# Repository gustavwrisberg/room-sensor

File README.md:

# Room Sensor Lite

A small, low-cost Home Assistant room sensor: **mmWave presence, temperature, humidity and light** on one fully assembled board, in a 3D-printed case that mounts on a wall, a ceiling, a room corner or a desk foot.

Runs [ESPHome](https://esphome.io), plugs in over USB-C, and is designed so the whole board can be assembled by JLCPCB with **Economic PCBA**: no soldering needed, you only screw the case shut.

## Features

| | |
|---|---|
| Presence | Hi-Link **HLK-LD2410C** 24 GHz radar, moving + still targets, ~6 m, ±60° |
| Temperature / humidity | **SHT40**-compatible sensor (Nyfea SHT40-N-NF) in its own vented chamber |
| Window detection | Template sensor in ESPHome: flags a sudden temperature drop |
| Light | **BH1750** behind a light tube and front window |
| MCU | **Seeed XIAO ESP32C6**: Wi-Fi 6, BLE, Thread-capable, onboard antenna + U.FL option |
| Power | 5 V over the XIAO's USB-C |
| Board | 43.3 × 22 mm, 2 layers, single-sided assembly |
| Case | 76 × 29 × 16 mm, resin print, 2 × M3×12 screws, keyholes in the back |

> IKEA MYGGBETT door/window sensors are deliberately **not** used: windows/doors are detected from the temperature drop instead.

## Repository layout

```
hardware/kicad/        KiCad 10 project (schematic + PCB)
hardware/production/   Gerbers, BOM and pick-and-place for JLCPCB
enclosure/             Parametric case (Python + manifold3d) and ready-made STLs
firmware/              ESPHome configuration
docs/                  Images
```

## Bill of materials

All parts are fitted by JLCPCB (Economic PCBA, top side).

| Ref | Part | LCSC | Note |
|---|---|---|---|
| U2 | Seeed XIAO ESP32C6 | C27675191 | castellated, soldered flat |
| SM1 | HLK-LD2410C-P radar | C19723500 | pin header, overhangs the left board edge |
| U1 | Nyfea SHT40-N-NF | C54946589 | I2C 0x44 |
| U4 | ROHM BH1750FVI-TR | C78960 | I2C 0x23, exposed pad not soldered |
| C7 | 10 µF 0805 | C15850 | radar 5 V |
| C9, C11, C12 | 100 nF 0402 | C1525 | C12 = BH1750 DVI power-up reset |
| R8, R9 | 4.7 kΩ 0402 | C25900 | I2C pull-ups |

> The exported `hardware/production/bom.csv` has an empty LCSC field for U2. Enter **C27675191** for it when uploading to JLCPCB (or add the LCSC field to the XIAO symbol before re-exporting).

Per case: 2 × M3×12 socket-head screws (DIN 912, e.g. JLCMC EDLA-J2-M3-L12).

**Approximate cost** (5 units, Oct 2026, incl. shipping, excl. VAT): ≈ $22 per assembled board, plus the case print.

## Pin map (XIAO ESP32C6)

| XIAO | GPIO | Net |
|---|---|---|
| D2 | GPIO2 | RADAR_OUT |
| D3 | GPIO21 | BH1750 DVI |
| D4 | GPIO22 | SDA |
| D5 | GPIO23 | SCL |
| D6 | GPIO16 | ESP TX → radar RX |
| D7 | GPIO17 | ESP RX ← radar TX |
| 5V | VBUS | radar VCC |
| 3V3 | 3.3 V | SHT40, BH1750, pull-ups |

GPIO3 / GPIO14 are used internally by the XIAO's RF switch (set in the ESPHome config).

## Ordering the board (JLCPCB)

1. Upload `hardware/production/gerbers.zip`: 2 layers, 1.6 mm, **LeadFree HASL**.
2. Enable PCB assembly → **Economic**, top side.
3. Upload `bom.csv` and `positions.csv`. Set U2 to C27675191.
4. In the placement preview, check:
   - the XIAO's USB-C points out over the bottom board edge
   - the radar's antenna side (gold patches) faces **up**
   - the pin-1 marks of U1 and U4

## Enclosure

The STLs in `enclosure/` are ready to print. Resin (e.g. JLC3DP 9600) is the default; SLS nylon also works (set `MATERIAL = "nylon"` for a tighter screw pilot hole).

| File | What |
|---|---|
| `lite_base.stl` | wall side: board pins, end bosses, USB-C opening, vents, keyholes |
| `lite_lid.stl` | room side: radar corner pads, light tube, SHT40 chamber + vents, screw posts |
| `lite_foot.stl` | desk stand, hooks into the keyholes |
| `lite_corner_mount.stl` | 45° wedge for a room corner (best radar coverage) |

Assembly: drop the board onto the three pins in the base, put the lid on, and fit the two M3×12 screws from the back.

To change anything, edit the parameters at the top of `room_sensor_case_lite.py` and run:

```bash
pip install manifold3d trimesh numpy
python room_sensor_case_lite.py      # writes the STLs
python render_previews.py            # optional preview images (needs embreex + matplotlib)
```

**Check on your first build:** `RADAR_LIFT` (height of the radar above the board, default 2.5 mm) depends on the radar's pin header.

## Firmware

1. Copy `firmware/secrets.example.yaml` to `secrets.yaml` and fill it in.
2. Flash `firmware/room-sensor-lite.yaml` over USB-C the first time (ESPHome dashboard or web.esphome.io), then OTA.
3. Calibrate the temperature: compare with a reference thermometer for an hour and set `temp_offset`.
4. Tune the radar gates and timeouts in Home Assistant (LD2410 entities).

The config has been validated with ESPHome 2026.10 (`esphome config`).

## Status

Rev "Lite" A: first batch ordered, **not yet tested on real hardware**. Issues and pull requests welcome.

## License

- **Hardware** (`hardware/`, `enclosure/*.stl`): [CERN-OHL-S v2](LICENSE-HARDWARE). You may build, modify and sell it; modified versions you distribute must be released under the same license, with sources.
- **Software** (`firmware/`, `enclosure/*.py`): [MIT](LICENSE-SOFTWARE).

Footprints come from the Seeed Studio OPL KiCad library (XIAO) and EasyEDA / LCSC (other parts), which have their own terms.

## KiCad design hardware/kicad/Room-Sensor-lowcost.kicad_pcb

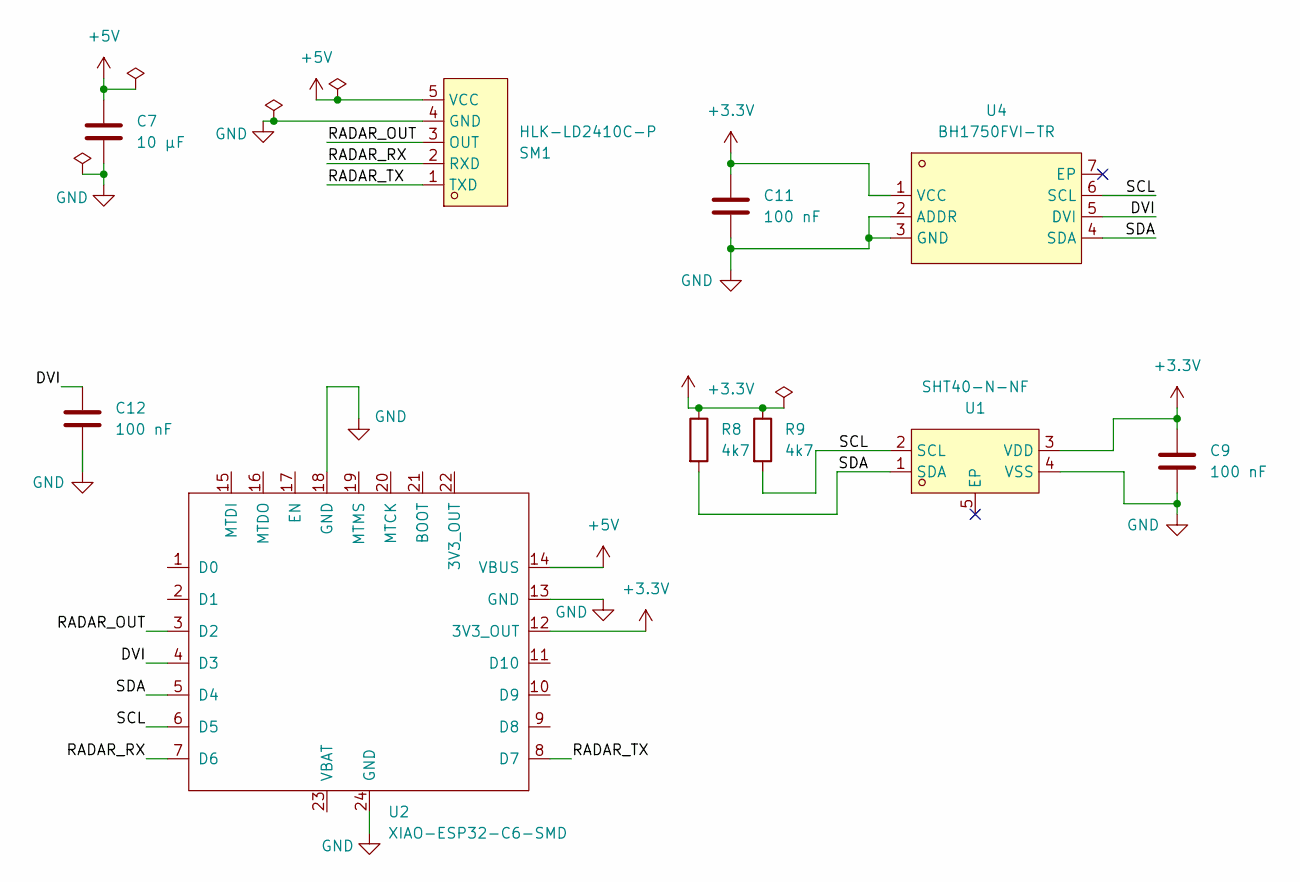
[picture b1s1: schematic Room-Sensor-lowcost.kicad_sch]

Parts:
C7: 10 µF; C_0805_2012Metric; LCSC Part C15850
C9, C11, C12: 100 nF; C_0402_1005Metric; LCSC Part C1525
R8, R9: 4k7; R_0402_1005Metric; LCSC Part C25900
SM1: HLK-LD2410C-P; SENSOR-TH_HLK-LD2410C-P; MPN HLK-LD2410C-P; LCSC Part C19723500
U1: SHT40-N-NF; DFN-4_L1.5-W1.5-P0.80-TL-EP; MPN SHT40-N-NF; LCSC Part C54946589
U2: XIAO-ESP32-C6-SMD; LCSC Part C27675191
U4: BH1750FVI-TR; WSOF-6_L2.6-W1.6-P0.50-TL-EP; MPN BH1750FVI-TR; LCSC Part C78960

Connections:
+3.3V: C9.1, C11.1, R8.1, R9.1, U1.3 (VDD), U2.12 (3V3_OUT), U4.1 (VCC)
+5V: C7.1, SM1.5 (VCC), U2.14 (VBUS)
/DVI: C12.1, U2.4 (D3), U4.5 (DVI)
/RADAR_OUT: SM1.3 (OUT), U2.3 (D2)
/RADAR_RX: SM1.2 (RXD), U2.7 (D6)
/RADAR_TX: SM1.1 (TXD), U2.8 (D7)
/SCL: R9.2, U1.2 (SCL), U2.6 (D5), U4.6 (SCL)
/SDA: R8.2, U1.1 (SDA), U2.5 (D4), U4.4 (SDA)
GND: C7.2, C9.2, C11.2, C12.2, SM1.4 (GND), U1.4 (VSS), U2.13 (GND), U2.18 (GND), U2.24 (GND), U4.2 (ADDR), U4.3 (GND)

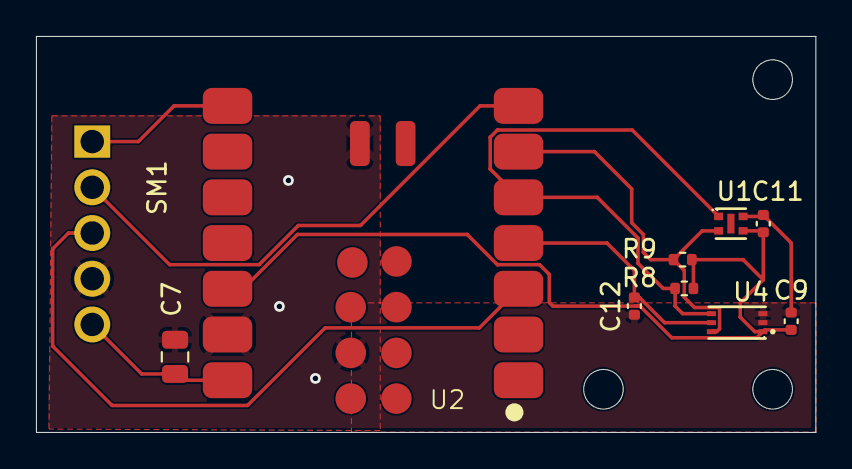
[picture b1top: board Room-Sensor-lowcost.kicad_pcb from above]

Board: 2 copper layers, 43.3 x 22.0 mm, 10 parts (0 on the bottom side), 9 nets.
